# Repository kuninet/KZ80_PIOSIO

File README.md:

# [KZ80_ZilogIO] KZ80シリーズ PIO/SIO2/CTCボード

## 概要

- 本ボードはSBC8080バス、およびZ80用信号線バスにつなげてZ80のZilog社製周辺デバイスを動作させるものです。
- Z80-PIO、SIO/2、CTCを稼働させます。
- 詳しい説明は、以下のwikiをご覧ください。
    - https://github.com/kuninet/KZ80_PIOSIO/wiki

## 注意事項

- SBC8080バスだけでは信号線が足りないため、KZ80-CPUB v2.1以降のZ80専用制御線コネクタを前提にしています。
- 現在本ボードは試作段階です。今後とも回路図、プリントパターンが変更される可能性があります。

## ライセンスについて

- 本リポジトリのデータはMITライセンスで公開します。

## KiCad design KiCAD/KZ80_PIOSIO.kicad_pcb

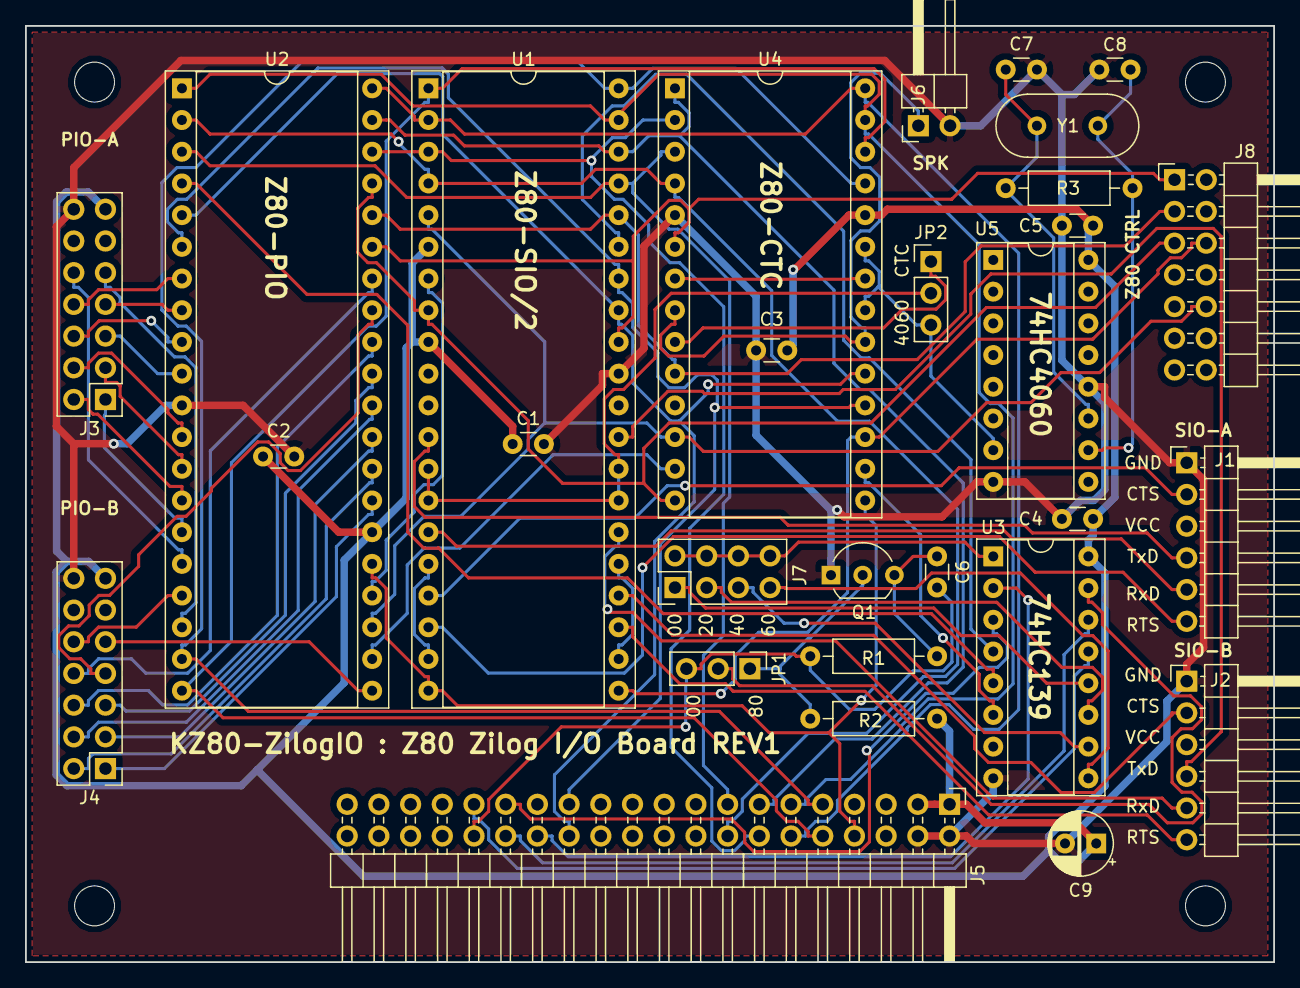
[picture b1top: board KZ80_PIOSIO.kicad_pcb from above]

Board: 2 copper layers, 100.0 x 75.0 mm, 33 parts (0 on the bottom side), 73 nets.

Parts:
C1, C2, C3, C4, C5: 0.1u; C_Disc_D3.0mm_W1.6mm_P2.50mm
C6, C7, C8: 22p; C_Disc_D3.0mm_W1.6mm_P2.50mm
C9: 10u; CP_Radial_D5.0mm_P2.50mm
J1: CON-A; PinHeader_1x06_P2.54mm_Horizontal
J2: CON-B; PinHeader_1x06_P2.54mm_Horizontal
J3: PIO-A; PinHeader_2x07_P2.54mm_Vertical
J4: PIO-B; PinHeader_2x07_P2.54mm_Vertical
J5: SBC8080 BUS; PinHeader_2x20_P2.54mm_Horizontal
J6: SPK_JP; PinHeader_1x02_P2.54mm_Horizontal
J7: ADDR-JP; PinHeader_2x04_P2.54mm_Vertical
J8: Z80 CONTROL; PinHeader_2x07_P2.54mm_Horizontal
JP1: A7 JP; PinHeader_1x03_P2.54mm_Vertical
JP2: SIO_JP; PinHeader_1x03_P2.54mm_Vertical
MH1, MH2, MH3, MH4: MountingHole; MountingHole_3.2mm_M3
Q1: 2SC1815; TO-92_Inline_Wide
R1: 100k; R_Axial_DIN0207_L6.3mm_D2.5mm_P10.16mm_Horizontal
R2: 1k; R_Axial_DIN0207_L6.3mm_D2.5mm_P10.16mm_Horizontal
R3: 1M; R_Axial_DIN0207_L6.3mm_D2.5mm_P10.16mm_Horizontal
U1: Z80-SIO2; DIP-40_W15.24mm_Socket
U2: Z80-PIO; DIP-40_W15.24mm_Socket
U3: 74HC139; DIP-16_W7.62mm_Socket
U4: Z80-CTC; DIP-28_W15.24mm_Socket
U5: 74HC4060; DIP-16_W7.62mm_Socket
Y1: 19.6608MHz; Crystal_HC49-4H_Vertical

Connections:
/D0: J5.9, U1.40, U2.19, U4.25
/D1: J5.10, U1.1, U2.20, U4.26
/D2: J5.11, U1.39, U2.1, U4.27
/D3: J5.12, U1.2, U2.40, U4.28
/D4: J5.13, U1.38, U2.39, U4.1
/D5: J5.14, U1.3, U2.38, U4.2
/D6: J5.15, U1.37, U2.3, U4.3
/D7: J5.16, U1.4, U2.2, U4.4
A0: J5.25, U1.34, U2.6, U4.18
A1: J5.26, U1.33, U2.5, U4.19
A3: J5.28, U3.2
A4: J5.29, U3.3
A5: J5.30, U3.14
A6: J5.31, U3.13
A7: C6.2, J5.32, JP1.3, R1.2
ARDY: J3.9, U2.18
BRDY: J4.9, U2.21
CLK: J5.8, U1.20, U2.25, U4.15
CTC-CE: U3.6, U4.16
CTSA: J1.6, U1.18
CTSB: J2.6, U1.23
GND: C1.2, C2.2, C3.2, C4.2, C5.2, C7.2, C8.2, C9.2, J1.1, J2.1, J3.14, J4.14, J5.2, J5.4, J6.2, Q1.1, U1.31, U2.11, U3.8, U4.5, U5.8, U5.12
unnamed: C6.1, Q1.3, R1.1
unnamed: C7.1, R3.1, U5.11, Y1.1
unnamed: C8.1, R3.2, U5.10, Y1.2
unnamed: J6.1, U4.8, U4.20
unnamed: J7.1, U3.12
unnamed: J7.2, J7.4, J7.6, J7.8, U3.1
unnamed: J7.3, U3.11
unnamed: J7.5, U3.10
unnamed: J7.7, U3.9
unnamed: JP1.1, Q1.2, R2.2
unnamed: JP1.2, U3.15
unnamed: JP2.1, U4.9
unnamed: JP2.3, U4.21, U4.23, U5.7
unnamed: U1.7, U2.24
unnamed: U1.16, U1.19
unnamed: U1.22, U1.25
unnamed: U2.22, U4.13
unnamed: U4.7, U4.22
PA0: J3.1, U2.15
PA1: J3.2, U2.14
PA2: J3.3, U2.13
PA3: J3.4, U2.12
PA4: J3.5, U2.10
PA5: J3.6, U2.9
PA6: J3.7, U2.8
PA7: J3.8, U2.7
PB0: J4.1, U2.27
PB1: J4.2, U2.28
PB2: J4.3, U2.29
PB3: J4.4, U2.30
PB4: J4.5, U2.31
PB5: J4.6, U2.32
PB6: J4.7, U2.33
PB7: J4.8, U2.34
PIO-CE: U2.4, U3.5
RTSA: J1.2, U1.17
RTSB: J2.2, U1.24
RxDA: J1.4, U1.12
RxDB: J2.4, U1.29
SIO-CE: U1.35, U3.4
SIO-CLK: JP2.2, U1.13, U1.14, U1.27, U1.28
TxDA: J1.5, U1.15
TxDB: J2.5, U1.26
VCC: C1.1, C2.1, C3.1, C4.1, C5.1, C9.1, J3.13, J4.13, J5.1, J5.3, R2.1, U1.6, U1.9, U2.26, U3.16, U4.24, U5.16
~ASTB: J3.10, U2.16
~BSTB: J4.10, U2.17
~INT-J: J8.10, U1.5, U2.23, U4.12
~IORQ: J8.3, U1.36, U2.36, U4.10
~M1: J8.5, U1.8, U2.37, U4.14
~RD: J8.1, U1.32, U2.35, U4.6
~RESET: J8.6, U1.21, U4.17

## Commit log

2019-05-14 Create LICENSE
2019-05-14 Rename LICENSE to LICENSE.txt
2019-05-15 REV1回路図、パターン作成
2019-05-16 CTC IEOをNC化 & プリントパターン見直し
2019-05-19 電源部に電解コンデンサ追加
2019-08-11 一部回路見直し&回路図出力
2019-09-05 パターン原点設定、ガーバーデータ再出力
2019-09-07 シルク間違い修正。ガーバーデータ出力項目変更。ガーバー再出力
2019-09-07 ガーバーデータ・リネーム実施
2019-09-09 シルク違い修正、ガーバーデータ再出力
2019-09-11 シルク見直し。ガーバーデータ再出力
2020-03-03 PIOを使用したソフトI2Cサンプル追加
2020-03-04 8255PPI用 I2Cモジュール作成
2020-03-04 8255PPI関係 ソース、ビルド作成
2020-03-04 アセンブル済み IntelHexファイル追加
2020-03-04 8255PPIによるI2C通信。実機テスト後のバグ修正
2020-03-04 PPI-I2C回路図修正
2023-10-21 PIO LED TESTプログラム作成
2023-10-21 PIO割り込みテストプログラム作成
2023-10-22 回路図修正
2023-10-28 不要なKiCADロックファイル削除
2023-11-02 PIO 入力基板回路改良
